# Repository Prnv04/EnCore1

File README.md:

# Encore 1.0 Pre-Qualifier Challenge - Buck Converter Design

### Overview

This repository contains the design, simulation, and PCB layout for a **Buck Converter** as part of the Encore 1.0 Pre-qualifier challenge. The objective of this challenge is to design a non-isolated buck converter with:

- **Input Voltage:** 24V (±2% tolerance)
- **Output Voltage:** 5V
- **Max Input Power:** 24W
- **Target Efficiency:** At least 90%

The project showcases the detailed steps of designing, simulating, and demonstrating a functional buck converter, focusing on power conversion efficiency.

### Problem Statement

The task is to design a **DC-DC Buck Converter** capable of converting a 24V input to a 5V output, with a target efficiency of at least 90%. The converter should handle up to **1A of current**, meaning the output power is 5W, and losses are minimized to ensure high efficiency.

The project includes:

1. **Schematic Design:** Created using KiCAD.
2. **Component Selection:** MOSFETs, capacitors, inductors, and switching ICs have been carefully selected based on voltage, current, and wattage ratings.
3. **Simulation:** The circuit has been simulated, and performance parameters such as efficiency and output voltage have been validated.
4. **PCB Layout:** Designed to fit within a **10 cm x 5 cm** form factor with a dual-layer PCB.
5. **Simulation Demonstration:** A video walkthrough explains the design and simulation results, uploaded to YouTube (Link shared below).

### Design Approach

- **MOSFET Selection:** Logic-level MOSFETs were chosen to act as switches based on high-side and low-side configurations. Power MOSFETs are employed to ensure efficient switching with minimal losses.
- **Switching Signal Source:** A 555 timer IC was used to generate the PWM signal required to control the switching operation of the MOSFETs.
- **Capacitor, Inductor, Resistor Ratings:** Each component is selected based on current, voltage, and wattage ratings to ensure the design meets performance and efficiency standards.
  
### Files in the Repository

- **Schematic Design Files:** Located in the `BUCK.kicad_sch` directory.
- **Component Calculations:** Detailed calculations for all components are documented in the `calculations/` folder.
- **Simulation Files:** Contains the KiCAD simulation files (`BuckConverterLT.asc` directory) and output data.
- **PCB Layout:** The PCB layout designed in Altium is available in the `pcb/` folder.
- **Video Demonstration:** A step-by-step explanation of the simulation results has been recorded and uploaded on YouTube.  
  [Video Link](https://youtu.be/VzP02CuskdQ)

### How to Use the Files

1. Clone the repository.
2. Open the KiCAD project files in the respective directories (`BUCK.kicad_sch` and `pcb/`).
3. Run the simulation to observe performance, efficiency, and output voltage characteristics.
4. Review the calculations for component selection to understand the design considerations.

### Team Members

- **Team Leader:** Pranaav Contractor
- **Team Member 1:** Prashant Singh
- **Team Member 2:** Meet Bhesaniya
- **Team Member 3:** Parth Vaghani

### License

This project is licensed under the MIT License. See the [LICENSE](LICENSE) file for details.

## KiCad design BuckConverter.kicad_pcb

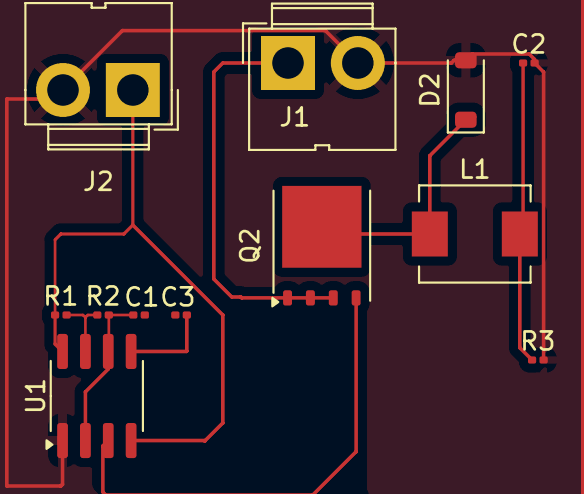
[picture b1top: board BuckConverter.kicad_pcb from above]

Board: 2 copper layers, 12 parts (0 on the bottom side), 9 nets.

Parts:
C1: 680p; C_0201_0603Metric
C2: 32u; C_0201_0603Metric
C3: 0.01u; C_0201_0603Metric
D2: PMEG4010BEA; D_SOD-123
J1, J2: Conn_01x02_Pin; JWT_A3963_1x02_P3.96mm_Vertical
L1: 37u; L_Neosid_SM-PIC0512H
Q2: BSC082N10LS; TDSON-8-1
R1: 2.2k; R_0201_0603Metric
R2: 9.1k; R_0201_0603Metric
R3: 1.16; R_0201_0603Metric
U1: ICM7555xB; SOIC-8_3.9x4.9mm_P1.27mm

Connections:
GND: C1.2, C2.2, C3.2, D2.2 (A), J1.2, J2.2, R3.2, U1.1 (GND)
unnamed: C2.1, L1.2, R3.1
unnamed: D2.1 (K), L1.1, Q2.5 (D)
unnamed: J1.1, Q2.1 (S), Q2.2 (S), Q2.3 (S)
unnamed: J2.1, R1.1, U1.4 (R), U1.8 (VCC)
unnamed: Q2.4 (G), U1.3 (Q)
unnamed: C3.1, U1.5 (CV)
unnamed: R1.2, R2.1, U1.7 (DIS)
unnamed: C1.1, R2.2, U1.2 (TR), U1.6 (THR)

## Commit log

2024-09-26 README.md
2024-09-26 Create Datasheets of Components
2024-09-27 Create datasheet
2024-09-27 Create temp
